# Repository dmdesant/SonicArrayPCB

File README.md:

# SonicArrayPCB
 Ultrasonic Parametric Array

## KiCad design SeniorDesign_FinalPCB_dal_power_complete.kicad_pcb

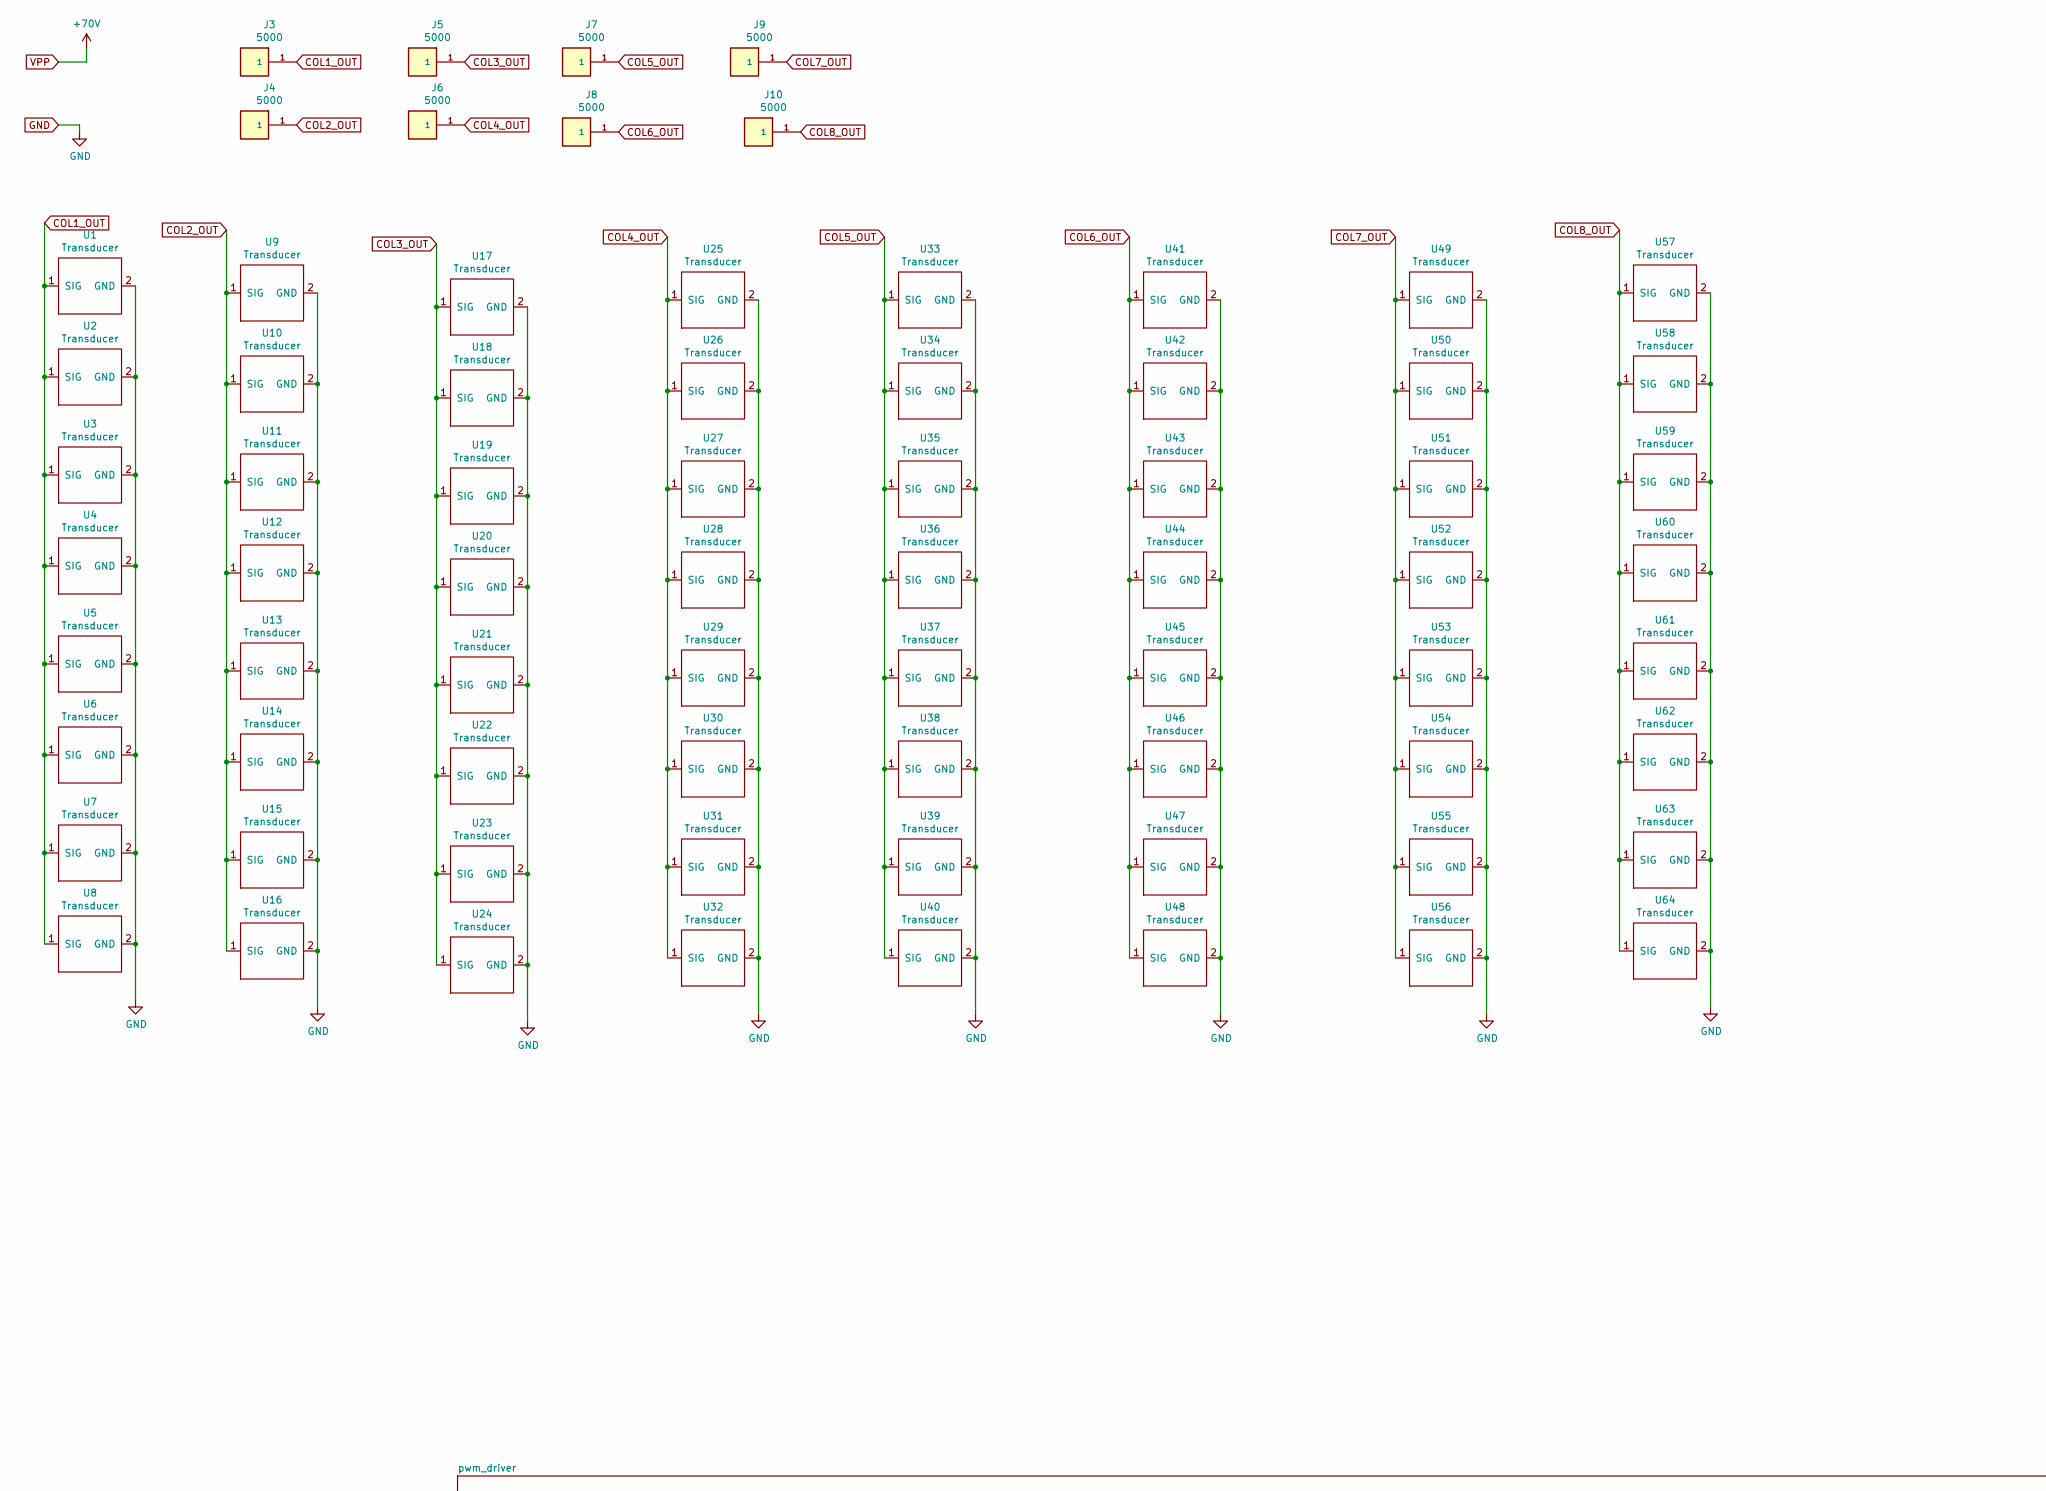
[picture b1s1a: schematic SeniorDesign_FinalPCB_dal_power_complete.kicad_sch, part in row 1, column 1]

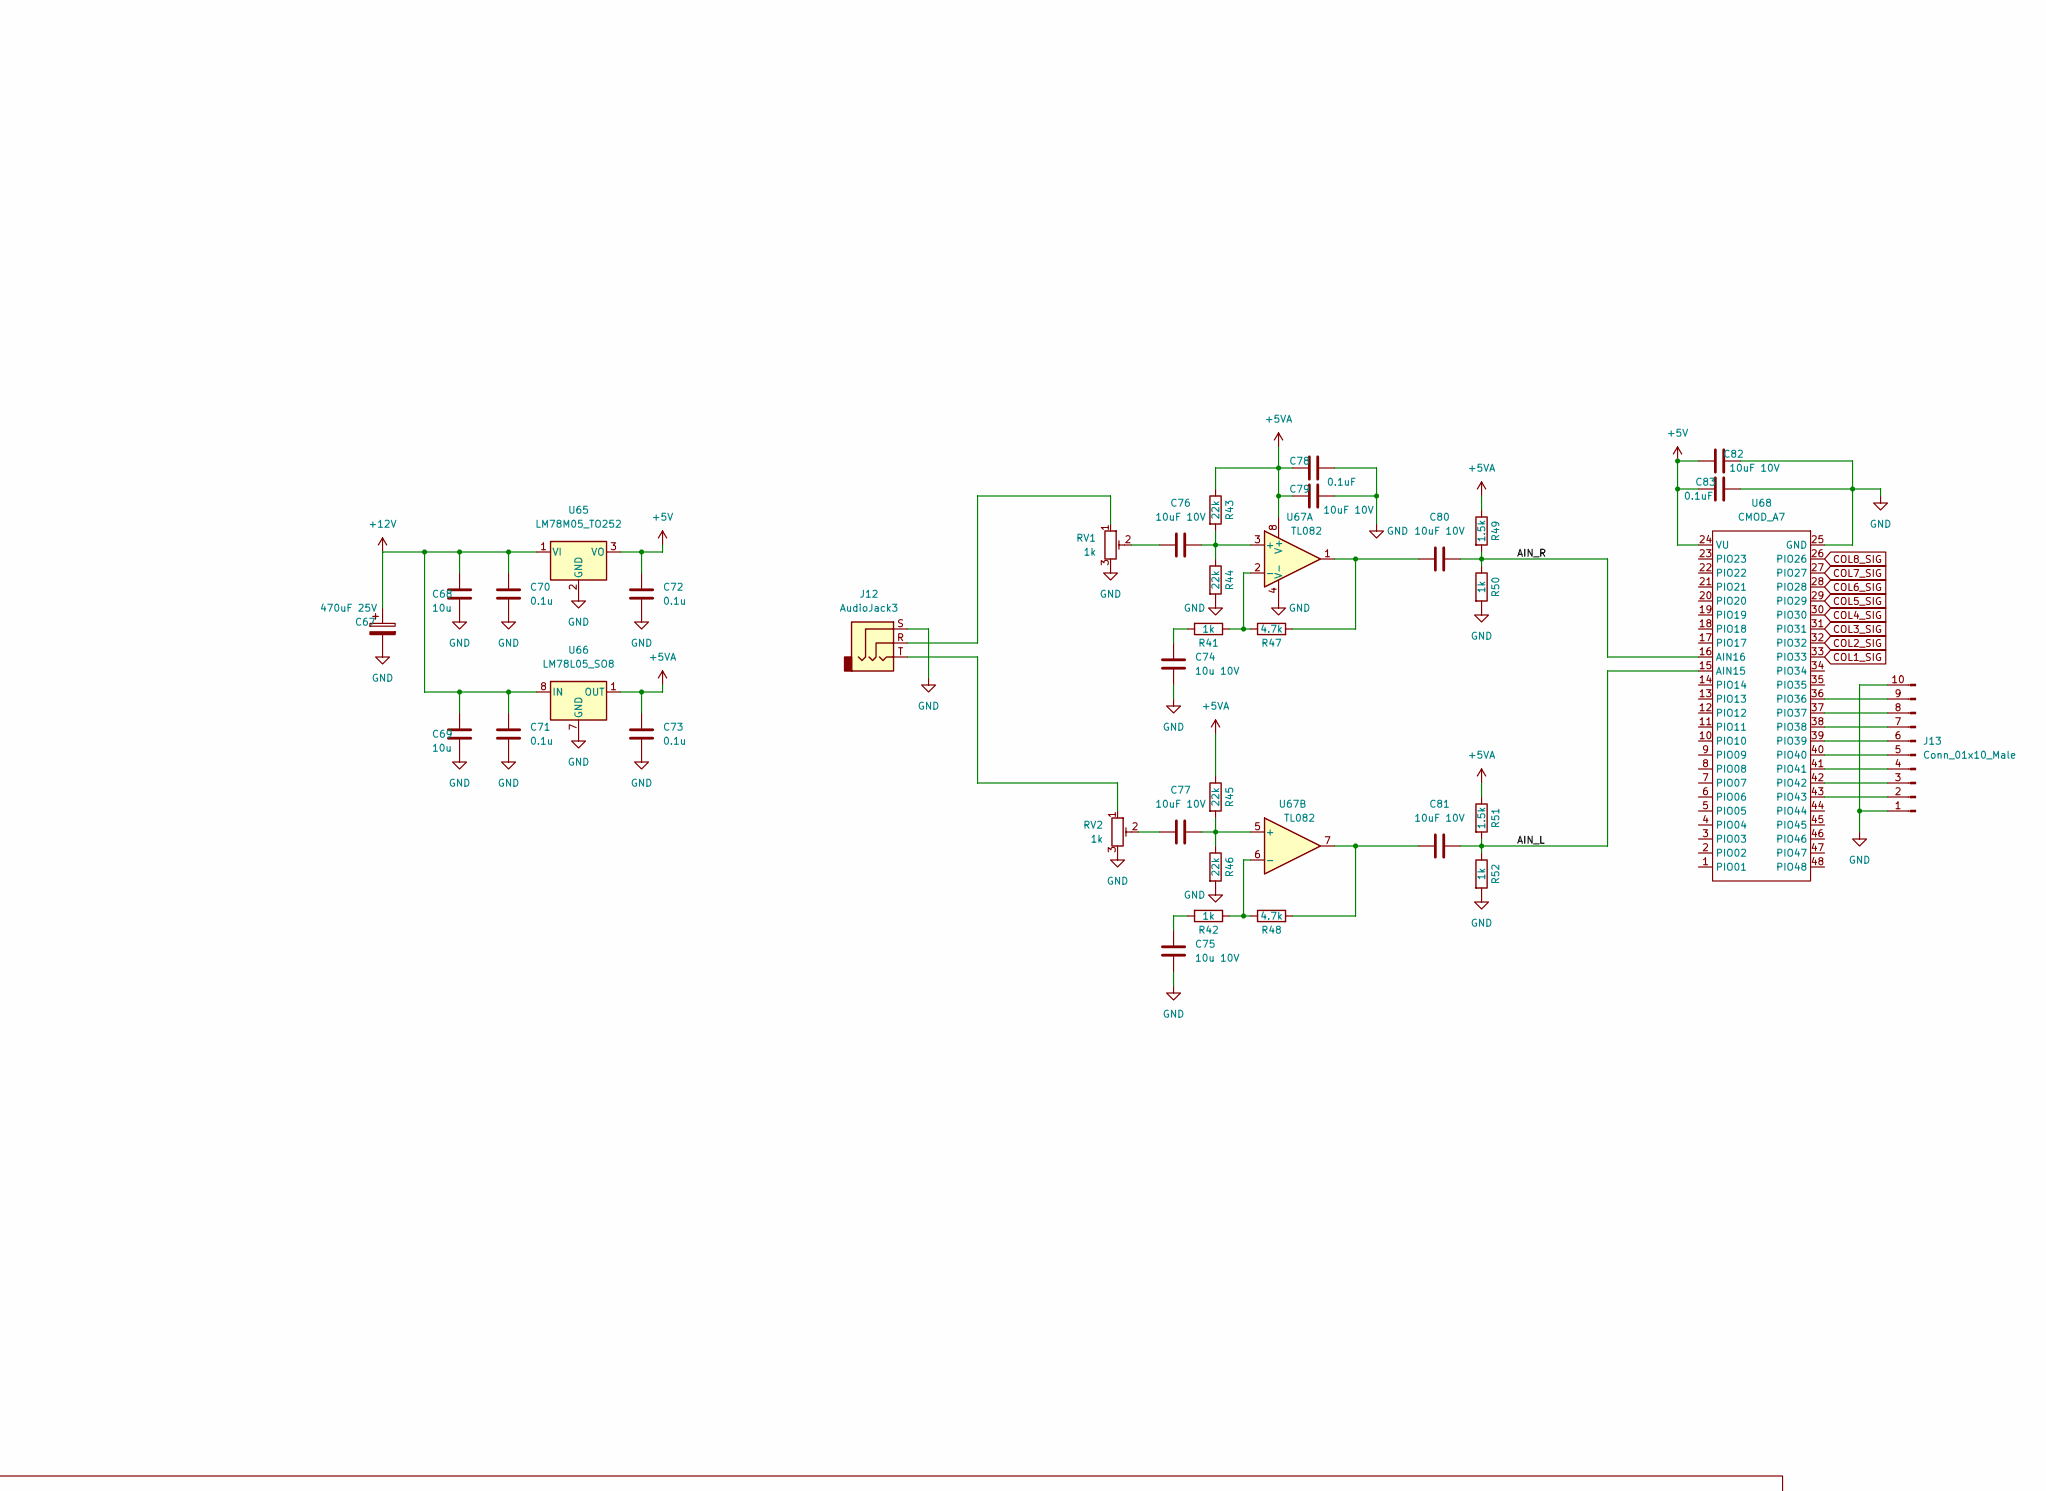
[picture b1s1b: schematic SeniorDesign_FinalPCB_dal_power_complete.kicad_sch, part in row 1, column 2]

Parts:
C67: 470uF 25V; CP_Elec_10x10
C68, C69: 10u; C_0603_1608Metric
C70, C71, C72, C73: 0.1u; C_0603_1608Metric
C74, C75: 10u 10V; C_0603_1608Metric; PartNum GMC10X5R106K10NT
C76, C77, C79, C80, C81, C82: 10uF 10V; C_0603_1608Metric
C78, C83: 0.1uF; C_0603_1608Metric
J3, J4, J5, J6, J7, J8, J9, J10: 5000; KEYSTONE_5000_TestPoint
J12: AudioJack3; Jack_3.5mm_CUI_SJ-3523-SMT_Horizontal
J13: Conn_01x10_Male; PinHeader_1x10_P2.54mm_Vertical
R41, R42, R50, R52: 1k; R_0603_1608Metric
R43, R44, R45, R46: 22k; R_0603_1608Metric
R47, R48: 4.7k; R_0603_1608Metric
R49, R51: 1.5k; R_0603_1608Metric
RV1, RV2: 1k; Potentiometer_Bourns_3314J_Vertical
U1, U2, U3, U4, U5, U6, U7, U8, U9, U10, U11, U12, U13, U14, U15, U16, U17, U18, U19, U20, U21, U22, U23, U24, U25, U26, U27, U28, U29, U30, U31, U32, U33, U34, U35, U36, U37, U38, U39, U40, U41, U42, U43, U44, U45, U46, U47, U48, U49, U50, U51, U52, U53, U54, U55, U56, U57, U58, U59, U60, U61, U62, U63, U64: Transducer
U65: LM78M05_TO252; TO-252-2
U66: LM78L05_SO8; SOIC-8_3.9x4.9mm_P1.27mm
U67: TL082; DIP-8_W7.62mm_LongPads
U68: CMOD_A7; CMOD A7

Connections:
+5V: C72.1, C82.1, C83.1, U65.3 (VO), U68.24 (VU)
+5VA: C73.1, C78.1, C79.1, R43.1, R45.1, R49.1, R51.1, U66.1 (OUT), U67.8 (V+)
/AIN_L: C81.2, R51.2, R52.1, U68.15 (AIN15)
/AIN_R: C80.2, R49.2, R50.1, U68.16 (AIN16)
COL1_OUT: J3.1, U1.1 (SIG), U2.1 (SIG), U3.1 (SIG), U4.1 (SIG), U5.1 (SIG), U6.1 (SIG), U7.1 (SIG), U8.1 (SIG); also elsewhere on the board
COL1_SIG: U68.33 (PIO33); also elsewhere on the board
COL2_OUT: J4.1, U9.1 (SIG), U10.1 (SIG), U11.1 (SIG), U12.1 (SIG), U13.1 (SIG), U14.1 (SIG), U15.1 (SIG), U16.1 (SIG); also elsewhere on the board
COL2_SIG: U68.32 (PIO32); also elsewhere on the board
COL3_OUT: J5.1, U17.1 (SIG), U18.1 (SIG), U19.1 (SIG), U20.1 (SIG), U21.1 (SIG), U22.1 (SIG), U23.1 (SIG), U24.1 (SIG); also elsewhere on the board
COL3_SIG: U68.31 (PIO31); also elsewhere on the board
COL4_OUT: J6.1, U25.1 (SIG), U26.1 (SIG), U27.1 (SIG), U28.1 (SIG), U29.1 (SIG), U30.1 (SIG), U31.1 (SIG), U32.1 (SIG); also elsewhere on the board
COL4_SIG: U68.30 (PIO30); also elsewhere on the board
COL5_OUT: J7.1, U33.1 (SIG), U34.1 (SIG), U35.1 (SIG), U36.1 (SIG), U37.1 (SIG), U38.1 (SIG), U39.1 (SIG), U40.1 (SIG); also elsewhere on the board
COL5_SIG: U68.29 (PIO29); also elsewhere on the board
COL6_OUT: J8.1, U41.1 (SIG), U42.1 (SIG), U43.1 (SIG), U44.1 (SIG), U45.1 (SIG), U46.1 (SIG), U47.1 (SIG), U48.1 (SIG); also elsewhere on the board
COL6_SIG: U68.28 (PIO28); also elsewhere on the board
COL7_OUT: J9.1, U49.1 (SIG), U50.1 (SIG), U51.1 (SIG), U52.1 (SIG), U53.1 (SIG), U54.1 (SIG), U55.1 (SIG), U56.1 (SIG); also elsewhere on the board
COL7_SIG: U68.27 (PIO27); also elsewhere on the board
COL8_OUT: J10.1, U57.1 (SIG), U58.1 (SIG), U59.1 (SIG), U60.1 (SIG), U61.1 (SIG), U62.1 (SIG), U63.1 (SIG), U64.1 (SIG); also elsewhere on the board
COL8_SIG: U68.26 (PIO26); also elsewhere on the board
unnamed: C74.2, R41.2
unnamed: C75.2, R42.2
unnamed: C76.1, RV1.2
unnamed: C76.2, R43.2, R44.1, U67.3 (+)
unnamed: C77.1, RV2.2
unnamed: C77.2, R45.2, R46.1, U67.5 (+)
unnamed: C80.1, R47.2, U67.1
unnamed: C81.1, R48.2, U67.7
unnamed: J12.R, RV1.1
unnamed: J12.T, RV2.1
unnamed: J13.2, U68.43 (PIO43)
unnamed: J13.3, U68.42 (PIO42)
unnamed: J13.4, U68.41 (PIO41)
unnamed: J13.5, U68.40 (PIO40)
unnamed: J13.6, U68.39 (PIO39)
unnamed: J13.7, U68.38 (PIO38)
unnamed: J13.8, U68.37 (PIO37)
unnamed: J13.9, U68.36 (PIO36)
unnamed: R41.1, R47.1, U67.2 (-)
unnamed: R42.1, R48.1, U67.6 (-)

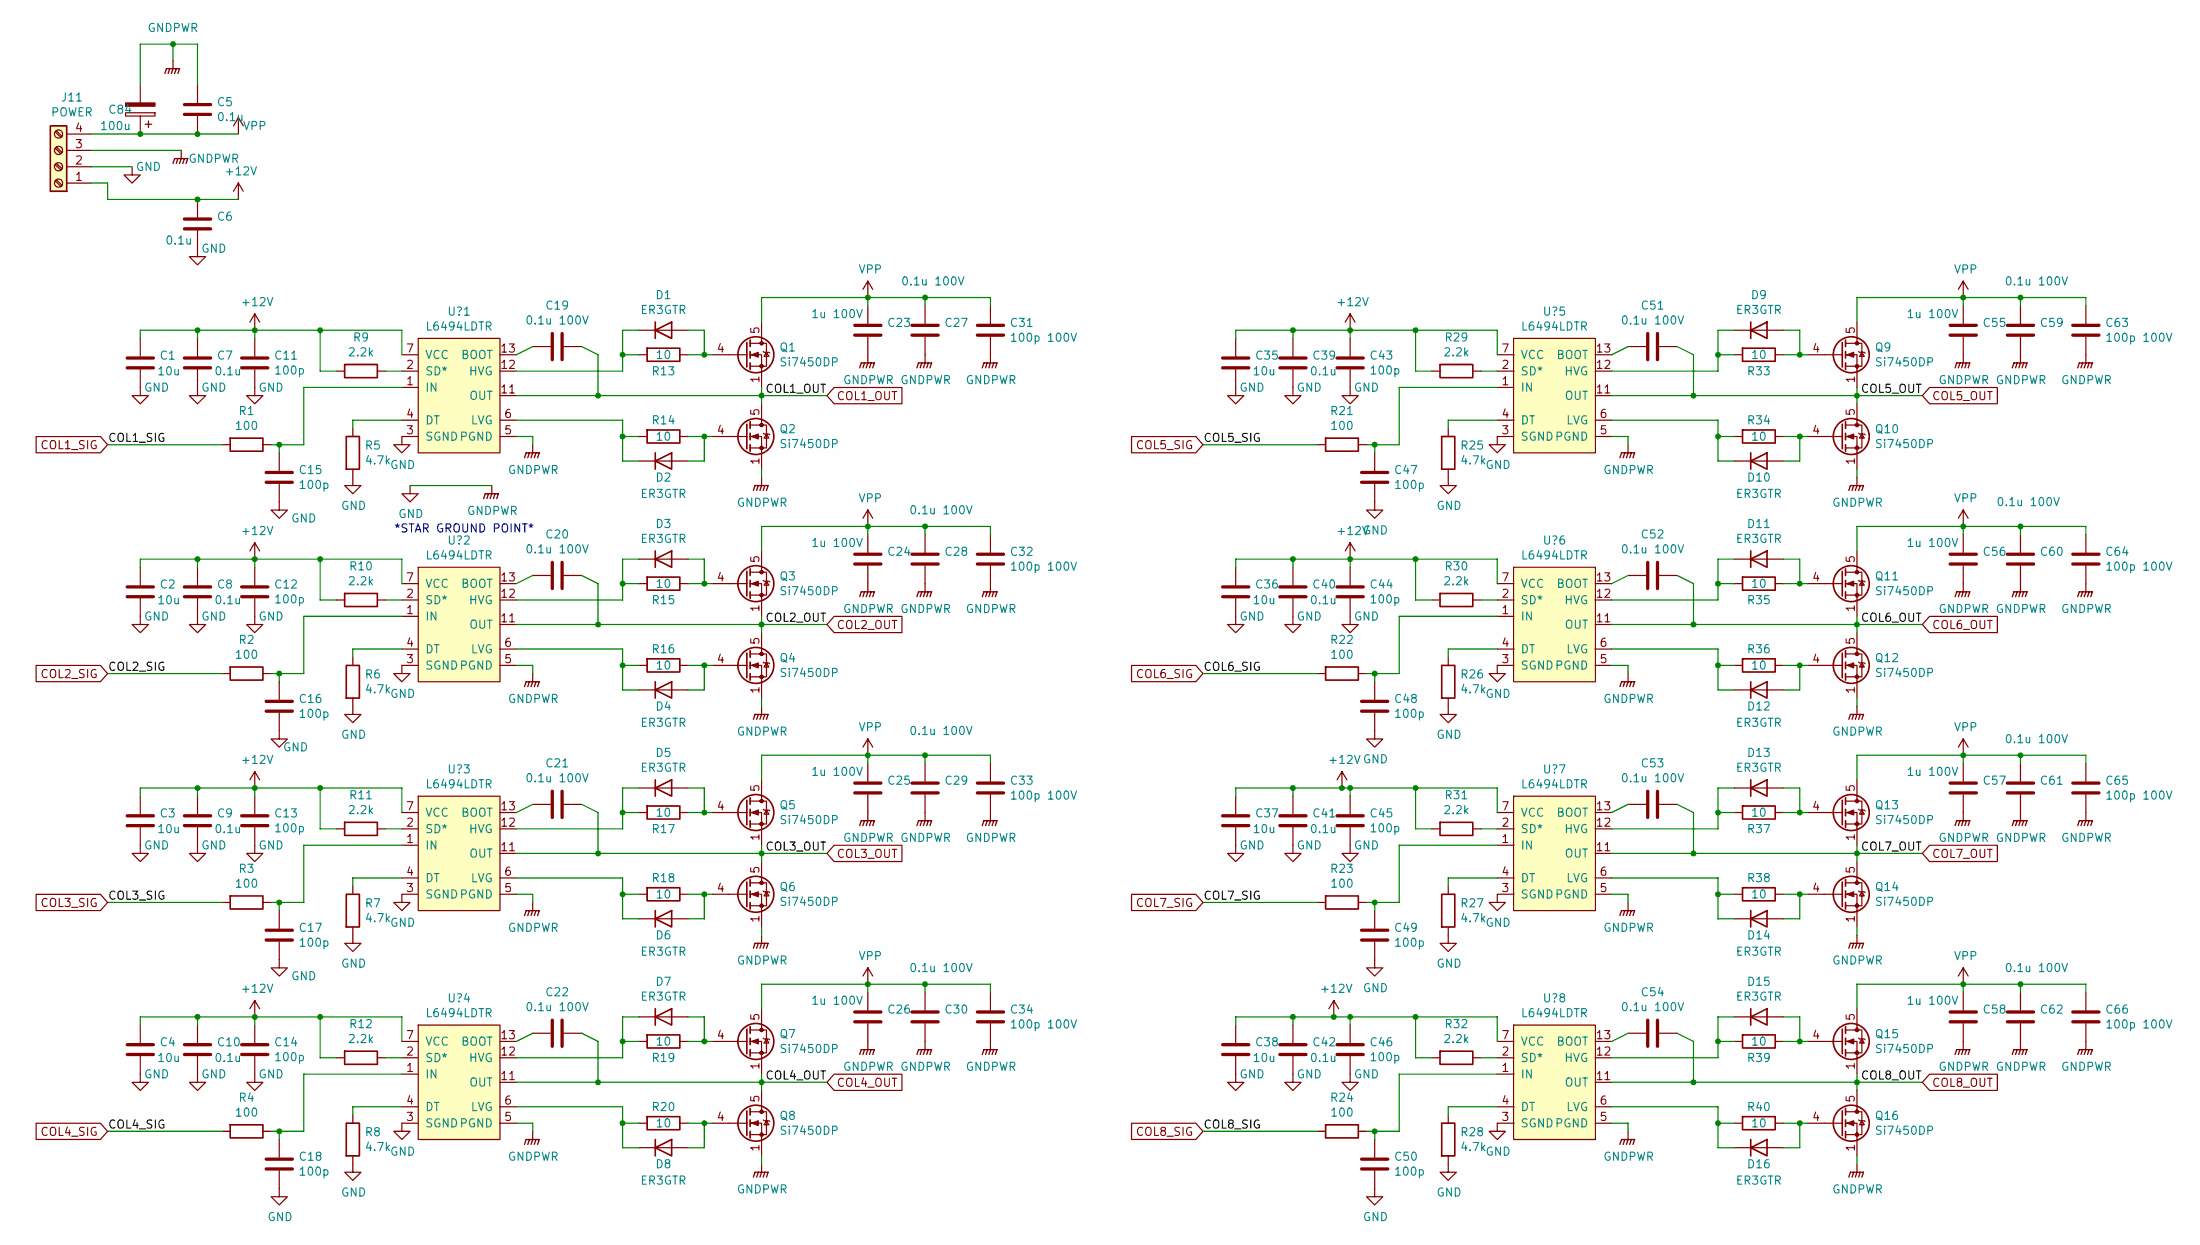
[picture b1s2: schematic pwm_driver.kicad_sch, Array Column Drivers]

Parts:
C1, C2, C3, C4, C35, C36, C37, C38: 10u; C_0603_1608Metric
C5: 0.1u; C_1206_3216Metric
C6, C7, C8, C9, C10, C39, C40, C41, C42: 0.1u; C_0603_1608Metric
C11, C12, C13, C14, C15, C16, C17, C18, C43, C44, C45, C46, C47, C48, C49, C50: 100p; C_0603_1608Metric
C19, C20, C21, C22, C51, C52, C53, C54: 0.1u 100V; C_0805_2012Metric
C23, C24, C25, C26, C55, C56, C57, C58: 1u 100V; C_1206_3216Metric
C27, C28, C29, C30, C59, C60, C61, C62: 0.1u 100V; C_1206_3216Metric
C31, C32, C33, C34, C63, C64, C65, C66: 100p 100V; C_1206_3216Metric
C84: 100u; CP_Radial_D18.0mm_P7.50mm
D1, D2, D3, D4, D5, D6, D7, D8, D9, D10, D11, D12, D13, D14, D15, D16: ER3GTR; D_SMC
J11: POWER; Screw Terminal 1x4
Q1, Q2, Q3, Q4, Q5, Q6, Q7, Q8, Q9, Q10, Q11, Q12, Q13, Q14, Q15, Q16: Si7450DP; PowerPAK_SO-8_Single
R1, R2, R3, R4, R21, R22, R23, R24: 100; R_0603_1608Metric
R5, R6, R7, R8, R25, R26, R27, R28: 4.7k; R_0603_1608Metric
R9, R10, R11, R12, R29, R30, R31, R32: 2.2k; R_0603_1608Metric
R13, R14, R15, R16, R17, R18, R19, R20, R33, R34, R35, R36, R37, R38, R39, R40: 10; R_0603_1608Metric
U?1, U?2, U?3, U?4, U?5, U?6, U?7, U?8: L6494LDTR

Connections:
COL1_OUT: C19.1, Q1.1 (S), Q1.2 (S), Q1.3 (S), Q2.5 (D), U?1.11 (OUT); also elsewhere on the board
COL1_SIG: R1.2; also elsewhere on the board
COL2_OUT: C20.1, Q3.1 (S), Q3.2 (S), Q3.3 (S), Q4.5 (D), U?2.11 (OUT); also elsewhere on the board
COL2_SIG: R2.2; also elsewhere on the board
COL3_OUT: C21.1, Q5.1 (S), Q5.2 (S), Q5.3 (S), Q6.5 (D), U?3.11 (OUT); also elsewhere on the board
COL3_SIG: R3.2; also elsewhere on the board
COL4_OUT: C22.1, Q7.1 (S), Q7.2 (S), Q7.3 (S), Q8.5 (D), U?4.11 (OUT); also elsewhere on the board
COL4_SIG: R4.2; also elsewhere on the board
COL5_OUT: C51.1, Q9.1 (S), Q9.2 (S), Q9.3 (S), Q10.5 (D), U?5.11 (OUT); also elsewhere on the board
COL5_SIG: R21.2; also elsewhere on the board
COL6_OUT: C52.1, Q11.1 (S), Q11.2 (S), Q11.3 (S), Q12.5 (D), U?6.11 (OUT); also elsewhere on the board
COL6_SIG: R22.2; also elsewhere on the board
COL7_OUT: C53.1, Q13.1 (S), Q13.2 (S), Q13.3 (S), Q14.5 (D), U?7.11 (OUT); also elsewhere on the board
COL7_SIG: R23.2; also elsewhere on the board
COL8_OUT: C54.1, Q15.1 (S), Q15.2 (S), Q15.3 (S), Q16.5 (D), U?8.11 (OUT); also elsewhere on the board
COL8_SIG: R24.2; also elsewhere on the board
unnamed: C15.2, R1.1, U?1.1 (IN)
unnamed: C16.2, R2.1, U?2.1 (IN)
unnamed: C17.2, R3.1, U?3.1 (IN)
unnamed: C18.2, R4.1, U?4.1 (IN)
unnamed: C19.2, U?1.13 (BOOT)
unnamed: C20.2, U?2.13 (BOOT)
unnamed: C21.2, U?3.13 (BOOT)
unnamed: C22.2, U?4.13 (BOOT)
unnamed: C47.2, R21.1, U?5.1 (IN)
unnamed: C48.2, R22.1, U?6.1 (IN)
unnamed: C49.2, R23.1, U?7.1 (IN)
unnamed: C50.2, R24.1, U?8.1 (IN)
unnamed: C51.2, U?5.13 (BOOT)
unnamed: C52.2, U?6.13 (BOOT)
unnamed: C53.2, U?7.13 (BOOT)
unnamed: C54.2, U?8.13 (BOOT)
unnamed: D1.1 (K), R13.2, U?1.12 (HVG)
unnamed: D1.2 (A), Q1.4 (G), R13.1
unnamed: D2.1 (K), R14.2, U?1.6 (LVG)
unnamed: D2.2 (A), Q2.4 (G), R14.1
unnamed: D3.1 (K), R15.2, U?2.12 (HVG)
unnamed: D3.2 (A), Q3.4 (G), R15.1
unnamed: D4.1 (K), R16.2, U?2.6 (LVG)
unnamed: D4.2 (A), Q4.4 (G), R16.1
unnamed: D5.1 (K), R17.2, U?3.12 (HVG)
unnamed: D5.2 (A), Q5.4 (G), R17.1
unnamed: D6.1 (K), R18.2, U?3.6 (LVG)
unnamed: D6.2 (A), Q6.4 (G), R18.1
unnamed: D7.1 (K), R19.2, U?4.12 (HVG)
unnamed: D7.2 (A), Q7.4 (G), R19.1
unnamed: D8.1 (K), R20.2, U?4.6 (LVG)
unnamed: D8.2 (A), Q8.4 (G), R20.1
unnamed: D9.1 (K), R33.2, U?5.12 (HVG)
unnamed: D9.2 (A), Q9.4 (G), R33.1
unnamed: D10.1 (K), R34.2, U?5.6 (LVG)
unnamed: D10.2 (A), Q10.4 (G), R34.1
unnamed: D11.1 (K), R35.2, U?6.12 (HVG)
unnamed: D11.2 (A), Q11.4 (G), R35.1
unnamed: D12.1 (K), R36.2, U?6.6 (LVG)
unnamed: D12.2 (A), Q12.4 (G), R36.1
unnamed: D13.1 (K), R37.2, U?7.12 (HVG)
unnamed: D13.2 (A), Q13.4 (G), R37.1
unnamed: D14.1 (K), R38.2, U?7.6 (LVG)
unnamed: D14.2 (A), Q14.4 (G), R38.1
unnamed: D15.1 (K), R39.2, U?8.12 (HVG)
unnamed: D15.2 (A), Q15.4 (G), R39.1
unnamed: D16.1 (K), R40.2, U?8.6 (LVG)
unnamed: D16.2 (A), Q16.4 (G), R40.1
unnamed: R5.1, U?1.4 (DT)
unnamed: R6.1, U?2.4 (DT)
unnamed: R7.1, U?3.4 (DT)
unnamed: R8.1, U?4.4 (DT)
unnamed: R9.1, U?1.2 (SD*)
unnamed: R10.1, U?2.2 (SD*)
unnamed: R11.1, U?3.2 (SD*)
unnamed: R12.1, U?4.2 (SD*)
unnamed: R25.1, U?5.4 (DT)
unnamed: R26.1, U?6.4 (DT)
unnamed: R27.1, U?7.4 (DT)
unnamed: R28.1, U?8.4 (DT)
unnamed: R29.1, U?5.2 (SD*)
unnamed: R30.1, U?6.2 (SD*)
unnamed: R31.1, U?7.2 (SD*)
unnamed: R32.1, U?8.2 (SD*)

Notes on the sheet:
*STAR GROUND POINT*

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
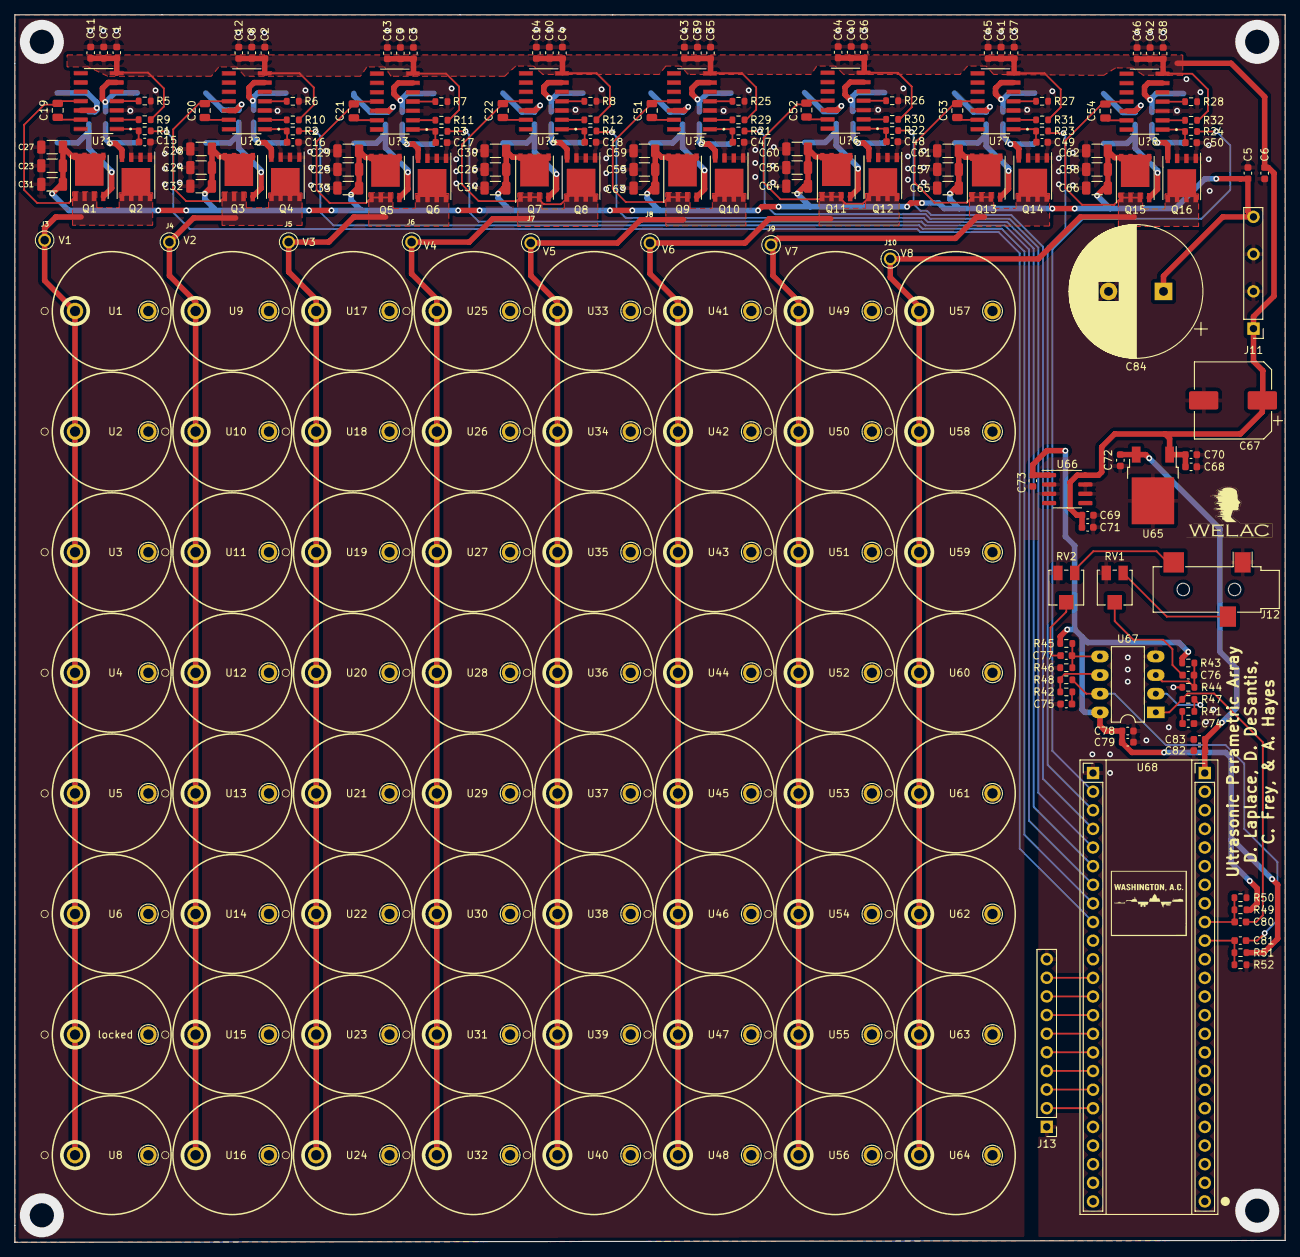
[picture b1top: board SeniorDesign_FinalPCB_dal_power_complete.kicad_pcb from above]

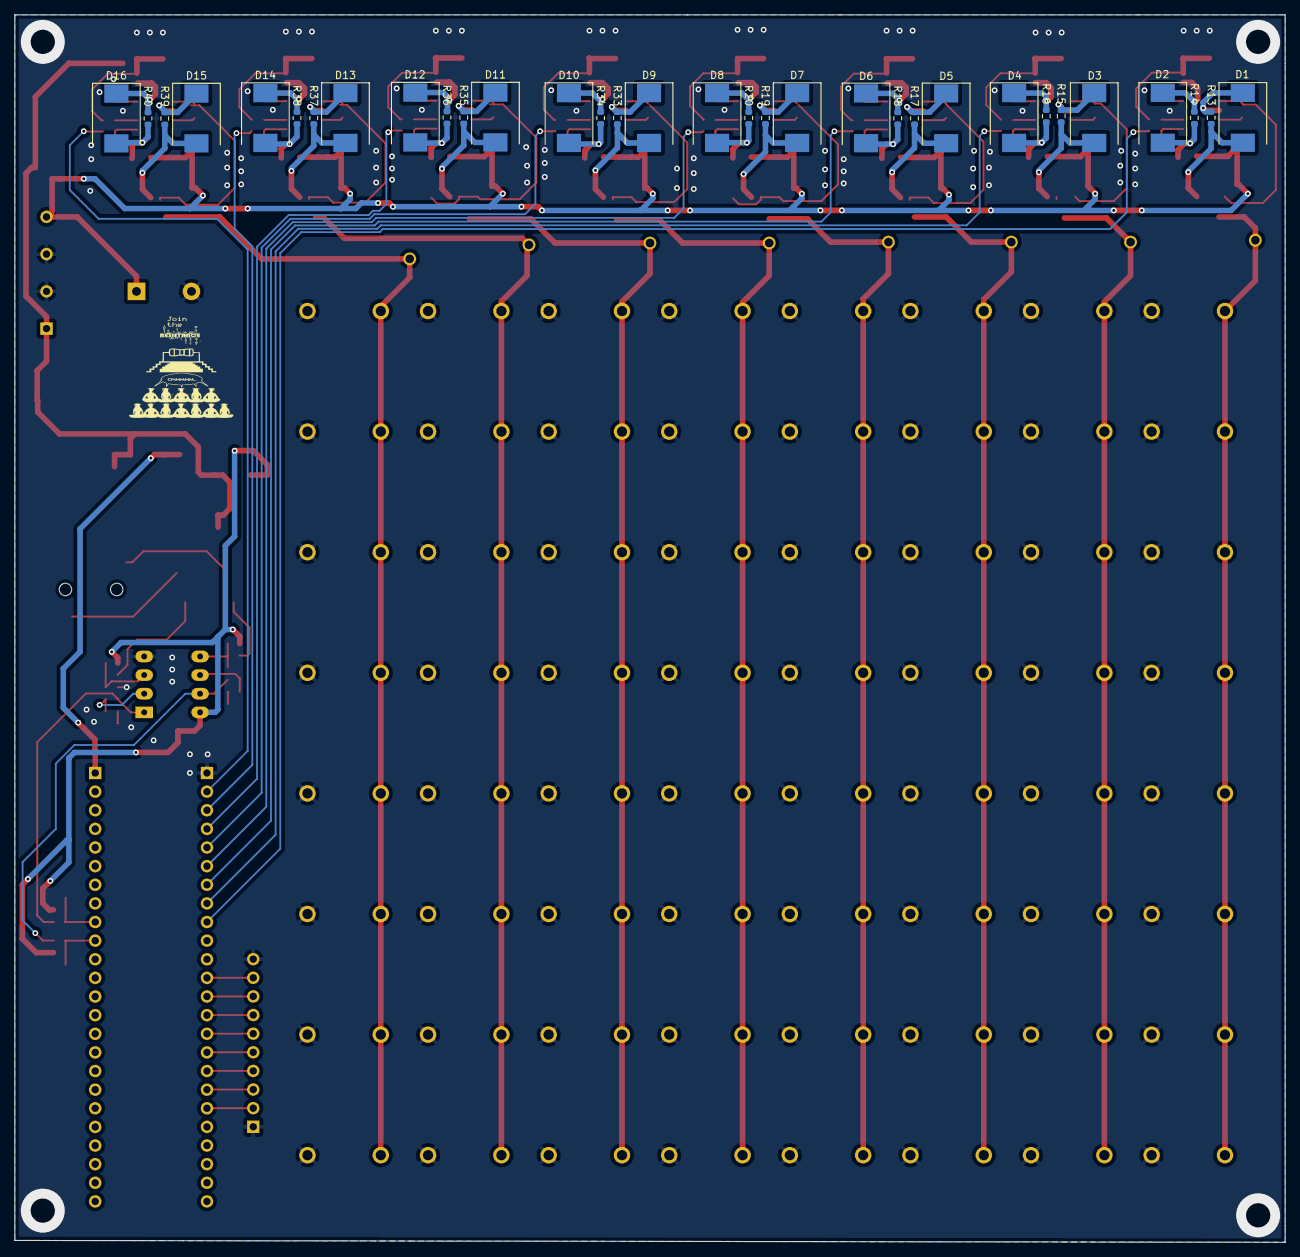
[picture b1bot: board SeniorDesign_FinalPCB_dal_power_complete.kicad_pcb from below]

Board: 2 copper layers, 173.2 x 167.4 mm, 257 parts (32 on the bottom side), 107 nets.

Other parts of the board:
locked: Transducer

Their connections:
COL1_OUT: locked.1 (SIG); also elsewhere on the board

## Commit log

2022-02-22 added files from source
2022-02-22 Add Footprint and Symbol Files
2022-02-22 Update CMOD A7 footprint
    Fixed an error in the CMOD A7 footprint.
2022-02-22 Update files for pcb
    Opened project prior to creation of git so all changes were not tracked.
2022-02-22 trace widths in amplifier channel adjusted
2022-02-22 Add WELAC Logo footprint
2022-02-24 Add the memes, temp place on board
    m e m e s
2022-02-24 Fixed transducer trace widths and via net names.
    Also adds WELAC logo and silkscreen board name + contributors
2022-02-24 channel 2 and 3 trace widths
2022-02-24 Finished trace widths on channels 4-8
2022-02-24 Rotate CMOD on pcb so usb points towards the edge.
2022-02-24 Fixed a via DRC error
    dan messed up :o
2022-02-25 all major components added, routing underway
    added and fixed some component footprints. routed column signals and designed/layout of audio amplifier and power supply. NEED TO CHECK CAP VOLTAGES
2022-02-26 Add 3D Models, Adjust components, Minor changes
    - Footprint for 1206 Capacitors is in the footprints folder
    - Added a mostly correct size transducer 3D model
    - Added the 3D model for the screw terminal
    - The above models are in a new folder called SeniorDesign_3DModels
    - Fixed some component placements and silkscreens that overlapped
    - Added 3D models for all resistors and capacitors of the power circuits
2022-02-27 Add missing traces
    Added traces on capacitors above the screw terminal
2022-03-01 Replaced 0603 Caps (VPP) with 1206
2022-03-01 Routing the rest of the things. (Subject to change)
    This is my attempt at routing all of the rest of the things. I used (Pcbnew / Tools / Cleanup Tracks & Via’s) to remove all of the small "unconnected track" warnings we were getting and in this confi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
2022-03-01 final pre-design review push
    Fixed some routing problems. Changed capacitor sizes for large bypass voltages. array modeled
2022-03-08 final send out
    sent out week of 2/28
